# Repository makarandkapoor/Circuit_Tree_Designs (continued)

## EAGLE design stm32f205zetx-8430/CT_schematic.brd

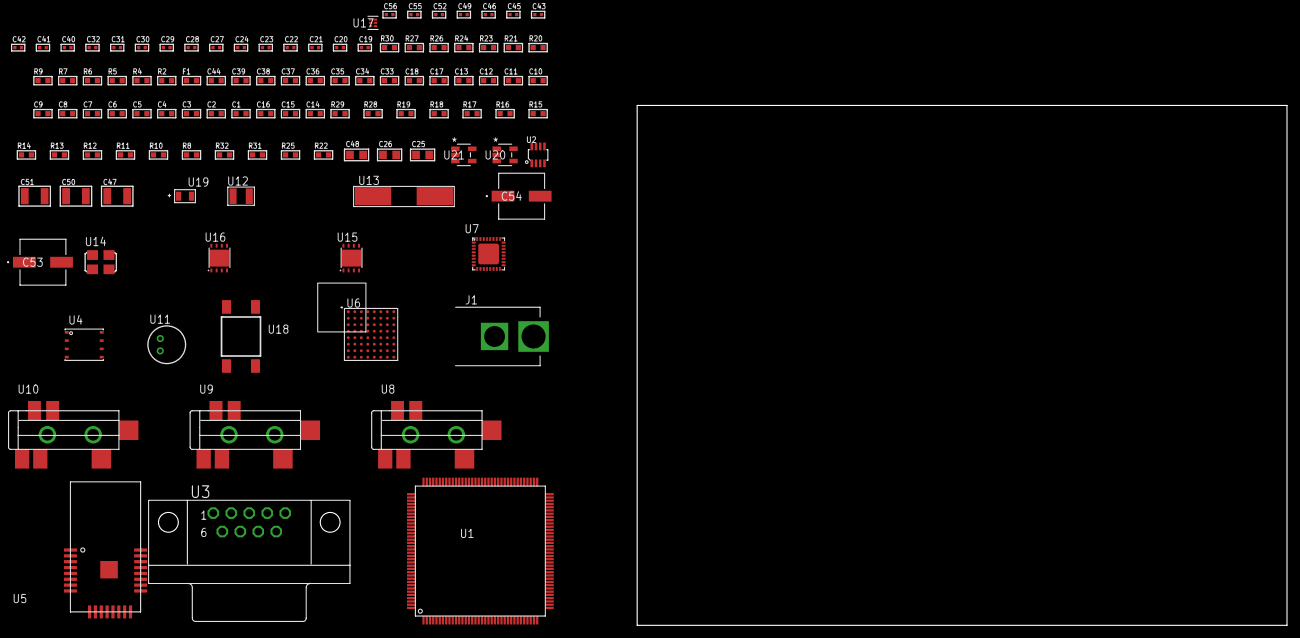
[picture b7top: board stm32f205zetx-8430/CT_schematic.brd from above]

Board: 2 copper layers, 100.0 x 80.0 mm, 109 parts (0 on the bottom side), 107 nets, no tracks yet.

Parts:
C1, C18, C33, C34, C35, C36, C37, C38, C39, C44: 1e-06; C0603
C2, C3, C4, C5, C6, C7, C8, C9, C10, C11, C12, C13: 1e-07; C0603
C14: 4.7e-06; C0603
C15, C16: 2.2e-06; C0603
C17: 1e-08; C0603
C19, C20, C21, C22: 1e-11; C0402
C23, C27, C29, C31, C40, C41, C42, C43, C52: 1e-07; C0402
C24, C28, C30, C32, C45, C46, C49, C55, C56: 1e-08; C0402
C25, C26, C48: 1e-05; C0805
C47, C50, C51: 1e-05; C1210
C53, C54: 0.0001; EXV-9H
F1: 240.0; L0603
J1: PJ-037B; PJ-037B_PACKAGE
R2, R24, R27: 1000.0; R0603
R4, R5: 4700.0; R0603
R6, R7: 2200.0; R0603
R8, R10, R11, R12, R13, R14, R15, R16, R17, R18, R19, R28, R29: 10000.0; R0603
R9: 120.0; R0603
R20, R21: 1270.0; R0603
R22, R25: 100000.0; R0603
R23: 200.0; R0603
R26: 2231.0; R0603
R30: 9100.0; R0603
R31: 680000.0; R0603
R32: 120000.0; R0603
U1: STM32F205ZET7; LQFP144
U2: MAX3051EKA+T; SOT-23-8
U3: 182-009-113R531; 182-009-MALE
U4: 24AA256-I/MF; DFN8-S
U5: ATBTLC1000-MR110CA
U6: PC28F512P33BFD
U7: SGTL5000XNAA3; QFN-32
U8, U9, U10: SJ-43515TS-SMT-TR
U11: WM-64PCT; WM-64PC
U12: ABS07-32.768KHZ-7-T
U13: ABLS-25.000MHZ-B2F-T
U14: ASFL-24.57MHZ-NCS; ASFL1
U15, U16: LP3878SDX-ADJ/NOPB; WSON-8
U17: TPS3895ADRYR; SON-6
U18: 4-1437565-2; SW_4-1437565-2
U19: Q65110A2395; LGM67K-G1J2-24-Z
U20, U21: nc7sz125m5x; NC7SZ125M5X

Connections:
CLK_CRYSTAL_U1_8: C19.1, U1.8, U12.1
CLK_CRYSTAL_U1_9: C20.1, U1.9, U12.2
CLK_CRYSTAL_U1_23: C21.1, U1.23, U13.1
CLK_CRYSTAL_U1_24: C22.1, U1.24, U13.2
CLK_U7_21: U7.21, U14.3
GND: C1.2, C2.2, C3.2, C4.2, C5.2, C6.2, C7.2, C8.2, C9.2, C10.2, C11.2, C12.2, C13.2, C14.2, C15.2, C16.2, C17.2, C18.2, C19.2, C20.2, C21.2, C22.2, C23.2, C24.2, C25.2, C26.2, C27.2, C28.2, C29.2, C30.2, C31.2, C32.2, C40.2, C41.2, C42.2, C43.2, C44.2, C45.2, C46.2, C47.2, C48.2, C49.2, C50.2, C51.2, C52.2, C53.2, C54.2, C55.2, C56.2, J1.2, R2.2, R8.2, R11.2, R21.2, R24.2, R27.2, R30.2, R32.2, U1.16, U1.31, U1.38, U1.51, U1.61, U1.83, U1.94, U1.107, U1.120, U1.130, U2.2, U2.8, U3.5, U4.4, U5.1, U5.9, U5.13, U5.24, U5.25, U6.B2, U6.H2, U6.H4, U6.H6, U7.1, U7.3, U7.7, U7.EXP, U9.1, U10.1, U11.2, U14.2, U15.3, U15.PAD, U16.3, U16.PAD, U17.2, U19.C, U20.1, U20.3, U21.1, U21.3
NET_U1_25: R5.1, U1.25, U21.4
NET_U1_33: C17.1, C18.1, F1.1, U1.32, U1.33
NET_U1_71: C15.1, U1.71
NET_U1_106: C16.1, U1.106
NET_U1_136: R6.1, U1.136, U4.6
NET_U1_138: R8.1, U1.138
NET_U1_140: R7.1, U1.140, U4.5
NET_U1_142: U18.3, U18.4
NET_U2_6: R9.2, U2.6
NET_U3_2: R9.2, U2.6, U3.2
NET_U3_3: R9.1, U2.7, U3.3
NET_U4_1: R10.1, U4.1
NET_U4_2: R11.1, U4.2
NET_U4_3: R12.1, U4.3
NET_U5_17: R13.1, U5.17
NET_U5_20: R14.1, U5.20
NET_U6_A4: C31.1, C32.1, U6.A4
NET_U6_C6: R18.1, U6.C6
NET_U6_D4: R4.1, U6.D4, U20.4
NET_U7_10: C43.1, U7.10
NET_U7_29: R20.1, U7.29
NET_U7_31: R21.1, U7.31
NET_U8_1: U7.4, U8.1
NET_U8_2: U7.2, U8.2
NET_U8_5: U7.6, U8.5
NET_U9_2: C34.1, U9.2
NET_U9_5: C33.1, U9.5
NET_U10_2: C36.1, C37.1, U10.2
NET_U10_5: C35.1, U10.5
NET_U10_13: C36.2, C37.2
NET_U11_1: C38.1, C39.1, C44.1, U7.16, U11.1
NET_U11_15: C38.2, C39.2
NET_U15_1: C46.1, U15.1
NET_U15_6: R23.2, R24.1, U15.6
NET_U15_8: R22.1, U15.8
NET_U16_1: C49.1, U16.1
NET_U16_6: R26.2, R27.1, U16.6
NET_U16_8: R25.1, U16.8
NET_U17_1: R29.1, R30.1, U17.1
NET_U17_3: R31.2, R32.1, U17.3
NET_U17_4: R28.1, U17.4, U20.2, U21.2
NET_U18_1: R2.1, U18.1, U18.2
PROC_CAN1_RX: U1.103, U2.4
PROC_CAN1_TX: U1.104, U2.1
PROC_FSMC_A0: U1.10, U6.A1
PROC_FSMC_A1: U1.11, U6.B1
PROC_FSMC_A2: U1.12, U6.C1
PROC_FSMC_A3: U1.13, U6.D1
PROC_FSMC_A4: U1.14, U6.D2
PROC_FSMC_A5: U1.15, U6.A2
PROC_FSMC_A6: U1.50, U6.C2
PROC_FSMC_A7: U1.53, U6.A3
PROC_FSMC_A8: U1.54, U6.B3
PROC_FSMC_A9: U1.55, U6.C3
PROC_FSMC_A10: U1.56, U6.D3
PROC_FSMC_A11: U1.57, U6.C4
PROC_FSMC_A12: U1.87, U6.A5
PROC_FSMC_A13: U1.88, U6.B5
PROC_FSMC_A14: U1.89, U6.C5
PROC_FSMC_A15: U1.90, U6.D7
PROC_FSMC_A16: U1.80, U6.D8
PROC_FSMC_A17: U1.81, U6.A7
PROC_FSMC_A18: U1.82, U6.B7
PROC_FSMC_A19: U1.2, U6.C7
PROC_FSMC_A20: U1.3, U6.C8
PROC_FSMC_A21: U1.4, U6.A8
PROC_FSMC_A22: U1.5, U6.G1
PROC_FSMC_A23: U1.1, U6.H8
PROC_FSMC_A24: U1.128, U6.B6
PROC_FSMC_CLK: U1.117, U6.E6
PROC_FSMC_D0: U1.85, U6.F2
PROC_FSMC_D1: U1.86, U6.E2
PROC_FSMC_D2: U1.114, U6.G3
PROC_FSMC_D3: U1.115, U6.E4
PROC_FSMC_D4: U1.58, U6.E5
PROC_FSMC_D5: U1.59, U6.G5
PROC_FSMC_D6: U1.60, U6.G6
PROC_FSMC_D7: U1.63, U6.H7
PROC_FSMC_D8: U1.64, U6.E1
PROC_FSMC_D9: U1.65, U6.E3
PROC_FSMC_D10: U1.66, U6.F3
PROC_FSMC_D11: U1.67, U6.F4
PROC_FSMC_D12: U1.68, U6.F5
PROC_FSMC_D13: U1.77, U6.H5
PROC_FSMC_D14: U1.78, U6.G7
PROC_FSMC_D15: U1.79, U6.E7
PROC_FSMC_NE1: R16.1, U1.123, U6.B4
PROC_FSMC_NL: R15.1, U1.137, U6.F6
PROC_FSMC_NOE: R17.1, U1.118, U6.F8
PROC_FSMC_NWAIT: U1.122, U6.F7
PROC_FSMC_NWE: R19.1, U1.119, U6.G8
PROC_I2S2_SCK: U1.69, U7.24
PROC_I2S2_SD: U1.29, U7.26
PROC_I2S2_WS: U1.73, U7.23
PROC_SPI1_MISO: U1.42, U5.14
PROC_SPI1_MOSI: U1.43, U5.11
PROC_SPI1_NSS: U1.40, U5.12
PROC_SPI1_SCK: U1.41, U5.10
VCC_S1_13V2: C47.1, C50.1, C53.1, C54.1, J1.1, R22.2, R25.2, U15.4, U16.4
VCC_TIER1_1V2: C40.1, C48.1, R23.1, U7.30, U15.5
VCC_TIER1_3V3: C1.1, C2.1, C3.1, C4.1, C5.1, C6.1, C7.1, C8.1, C9.1, C10.1, C11.1, C12.1, C13.1, C14.1, C23.1, C24.1, C25.1, C26.1, C27.1, C28.1, C29.1, C30.1, C41.1, C42.1, C45.1, C51.1, C52.1, C55.1, C56.1, F1.2, R4.2, R5.2, R6.2, R7.2, R10.2, R12.2, R13.2, R14.2, R15.2, R16.2, R17.2, R18.2, R19.2, R20.2, R26.1, R28.2, R29.2, R31.1, U1.6, U1.17, U1.30, U1.39, U1.52, U1.62, U1.72, U1.84, U1.95, U1.108, U1.121, U1.131, U1.144, U2.3, U4.7, U4.8, U5.6, U5.22, U6.A6, U6.D5, U6.D6, U6.G4, U6.H3, U7.5, U7.20, U14.4, U16.5, U17.6, U20.5, U21.5

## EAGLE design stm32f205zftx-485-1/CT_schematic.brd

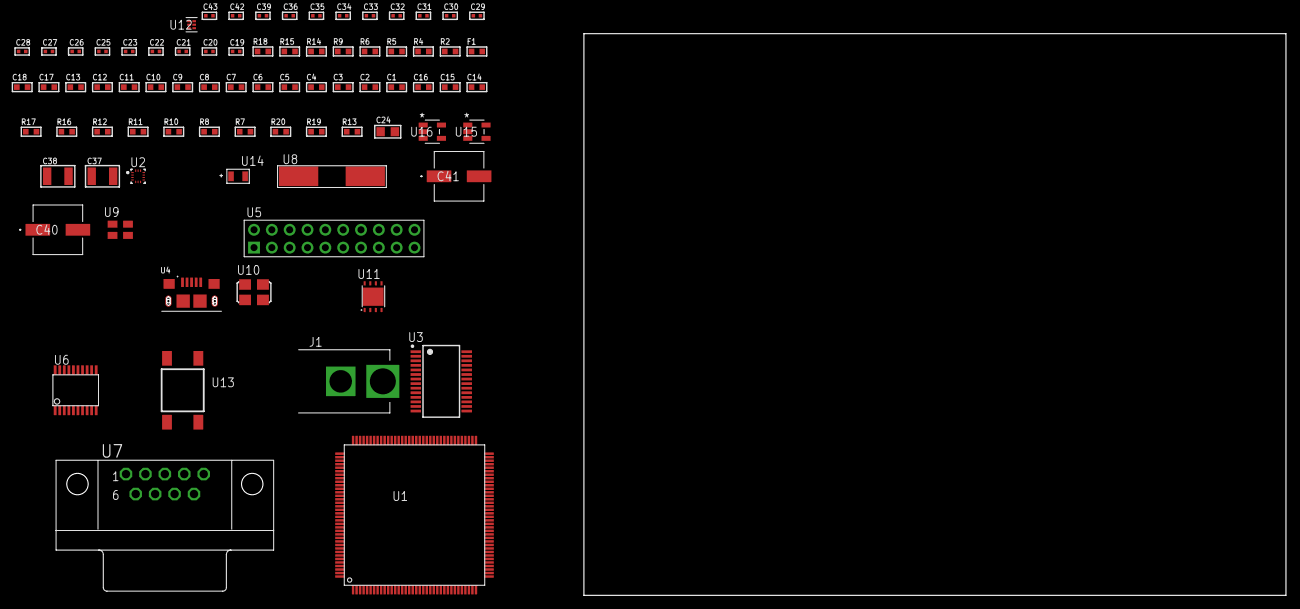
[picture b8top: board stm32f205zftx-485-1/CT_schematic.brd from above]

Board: 2 copper layers, 79 parts (0 on the bottom side), 46 nets, no tracks yet.

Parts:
C1, C18: 1e-06; C0603
C2, C3, C4, C5, C6, C7, C8, C9, C10, C11, C12, C13: 1e-07; C0603
C14: 4.7e-06; C0603
C15, C16: 2.2e-06; C0603
C17: 1e-08; C0603
C19, C20: 1e-11; C0402
C21, C22, C23, C25, C26, C27, C28, C29, C30, C31, C32, C33, C39: 1e-07; C0402
C24: 4.7e-06; C0805
C34, C35, C36, C42, C43: 1e-08; C0402
C37, C38: 1e-05; C1210
C40, C41: 0.0001; EXV-9H
F1: 240.0; L0603
J1: PJ-037B; PJ-037B_PACKAGE
R2, R15: 1000.0; R0603
R4, R9: 4700.0; R0603
R5, R6: 2200.0; R0603
R7, R8, R10, R11, R12, R16, R17: 10000.0; R0603
R13: 100000.0; R0603
R14: 2231.0; R0603
R18: 9100.0; R0603
R19: 680000.0; R0603
R20: 120000.0; R0603
U1: STM32F205ZFT6; LQFP144
U2: BMC150; LGA14R35P5X6_200X200X100
U3: FT232RL-REEL; SSOP-28
U4: 10118193-0001LF; FCI_10118193-0001LF
U5: TST-110-05-T-D-RA
U6: SP3203ECY-L/TR; TSSOP20-I
U7: 182-009-113R531; 182-009-MALE
U8: ABLS-25.000MHZ-B2F-T
U9: ASEK-32.768KHz-ECST; ASEK
U10: ASFL1-12MHZ-NCS; ASFL1
U11: LP3878SDX-ADJ/NOPB; WSON-8
U12: TPS3895ADRYR; SON-6
U13: 4-1437565-2; SW_4-1437565-2
U14: Q65110A2395; LGM67K-G1J2-24-Z
U15, U16: nc7sz125m5x; NC7SZ125M5X

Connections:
CLK_CRYSTAL_U1_23: C19.1, U1.23, U8.1
CLK_CRYSTAL_U1_24: C20.1, U1.24, U8.2
CLK_U1_8: U1.8, U9.3
CLK_U3_27: U3.27, U10.3
GND: C1.2, C2.2, C3.2, C4.2, C5.2, C6.2, C7.2, C8.2, C9.2, C10.2, C11.2, C12.2, C13.2, C14.2, C15.2, C16.2, C17.2, C18.2, C19.2, C20.2, C21.2, C22.2, C23.2, C24.2, C25.2, C26.2, C27.2, C28.2, C29.2, C32.2, C33.2, C34.2, C35.2, C36.2, C37.2, C38.2, C39.2, C40.2, C41.2, C42.2, C43.2, J1.2, R2.2, R7.2, R11.2, R15.2, R18.2, R20.2, U1.16, U1.31, U1.38, U1.51, U1.61, U1.83, U1.94, U1.107, U1.120, U1.130, U2.1, U2.6, U2.7, U2.9, U3.7, U3.18, U3.21, U3.25, U3.26, U4.5, U4.6, U4.7, U4.8, U4.9, U5.4, U5.6, U5.8, U5.10, U5.12, U5.14, U5.16, U5.18, U5.20, U6.18, U7.5, U9.2, U10.2, U11.3, U11.PAD, U12.2, U14.C, U15.2, U15.3, U16.1, U16.3
NET_U1_25: R4.1, U1.25, U16.4
NET_U1_33: C17.1, C18.1, F1.1, U1.32, U1.33
NET_U1_71: C15.1, U1.71
NET_U1_106: C16.1, U1.106
NET_U1_136: R5.1, U1.136, U2.11
NET_U1_137: R6.1, U1.137, U2.14
NET_U1_138: R7.1, U1.138
NET_U1_142: U13.3, U13.4
NET_U3_14: R10.1, U3.14
NET_U3_17: C25.1, U3.17
NET_U3_19: R11.1, U3.19
NET_U4_1: R9.1, U4.1
NET_U4_2: U3.16, U4.2
NET_U4_3: U3.15, U4.3
NET_U6_1: C30.1, U6.1
NET_U6_2: C32.1, U6.2
NET_U6_3: C30.2, U6.3
NET_U6_4: C31.1, U6.4
NET_U6_5: C31.2, U6.5
NET_U6_6: C33.1, U6.6
NET_U7_2: U6.14, U7.2
NET_U7_3: U6.17, U7.3
NET_U7_7: U6.13, U7.7
NET_U7_8: U6.16, U7.8
NET_U11_1: C36.1, U11.1
NET_U11_6: R14.2, R15.1, U11.6
NET_U11_8: R13.1, U11.8
NET_U12_1: R17.1, R18.1, U12.1
NET_U12_3: R19.2, R20.1, U12.3
NET_U12_4: R16.1, U12.4, U15.4, U16.2
NET_U13_1: R2.1, U13.1, U13.2
PROC_SYS_JTCK_SWCLK: U1.109, U5.9
PROC_SYS_JTDO_SWO: U1.133, U5.13
PROC_SYS_JTMS_SWDIO: U1.105, U5.7
PROC_UART4_RX: U1.35, U3.1
PROC_UART4_TX: U1.34, U3.5
PROC_UART5_RX: U1.116, U6.11
PROC_UART5_TX: U1.113, U6.7
RST_OUT_U5_SRESET_B: R12.1, U5.15, U15.1
VCC_S1_13V8: C37.1, C40.1, C41.1, J1.1, R13.2, U11.4
VCC_TIER1_3V3: C1.1, C2.1, C3.1, C4.1, C5.1, C6.1, C7.1, C8.1, C9.1, C10.1, C11.1, C12.1, C13.1, C14.1, C21.1, C22.1, C23.1, C24.1, C26.1, C27.1, C28.1, C29.1, C34.1, C35.1, C38.1, C39.1, C42.1, C43.1, F1.2, R4.2, R5.2, R6.2, R8.1, R8.2, R10.2, R12.2, R14.1, R16.2, R17.2, R19.1, U1.6, U1.17, U1.30, U1.39, U1.52, U1.62, U1.72, U1.84, U1.95, U1.108, U1.121, U1.131, U1.144, U2.8, U2.10, U2.12, U2.13, U3.4, U3.20, U5.1, U6.12, U6.19, U9.4, U10.4, U11.5, U12.6, U15.5, U16.5
